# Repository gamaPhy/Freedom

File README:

## 3D Printing 
| Material      | Nozzle (C) | Bed (C) | Speed (mm/s) | First Layer speed | 
| ----------- | ----------- | -- | --| --|
| PLA+     | 220       | 50 | 60 | 40
| PETG   | 240        | 77 | 50 | 15

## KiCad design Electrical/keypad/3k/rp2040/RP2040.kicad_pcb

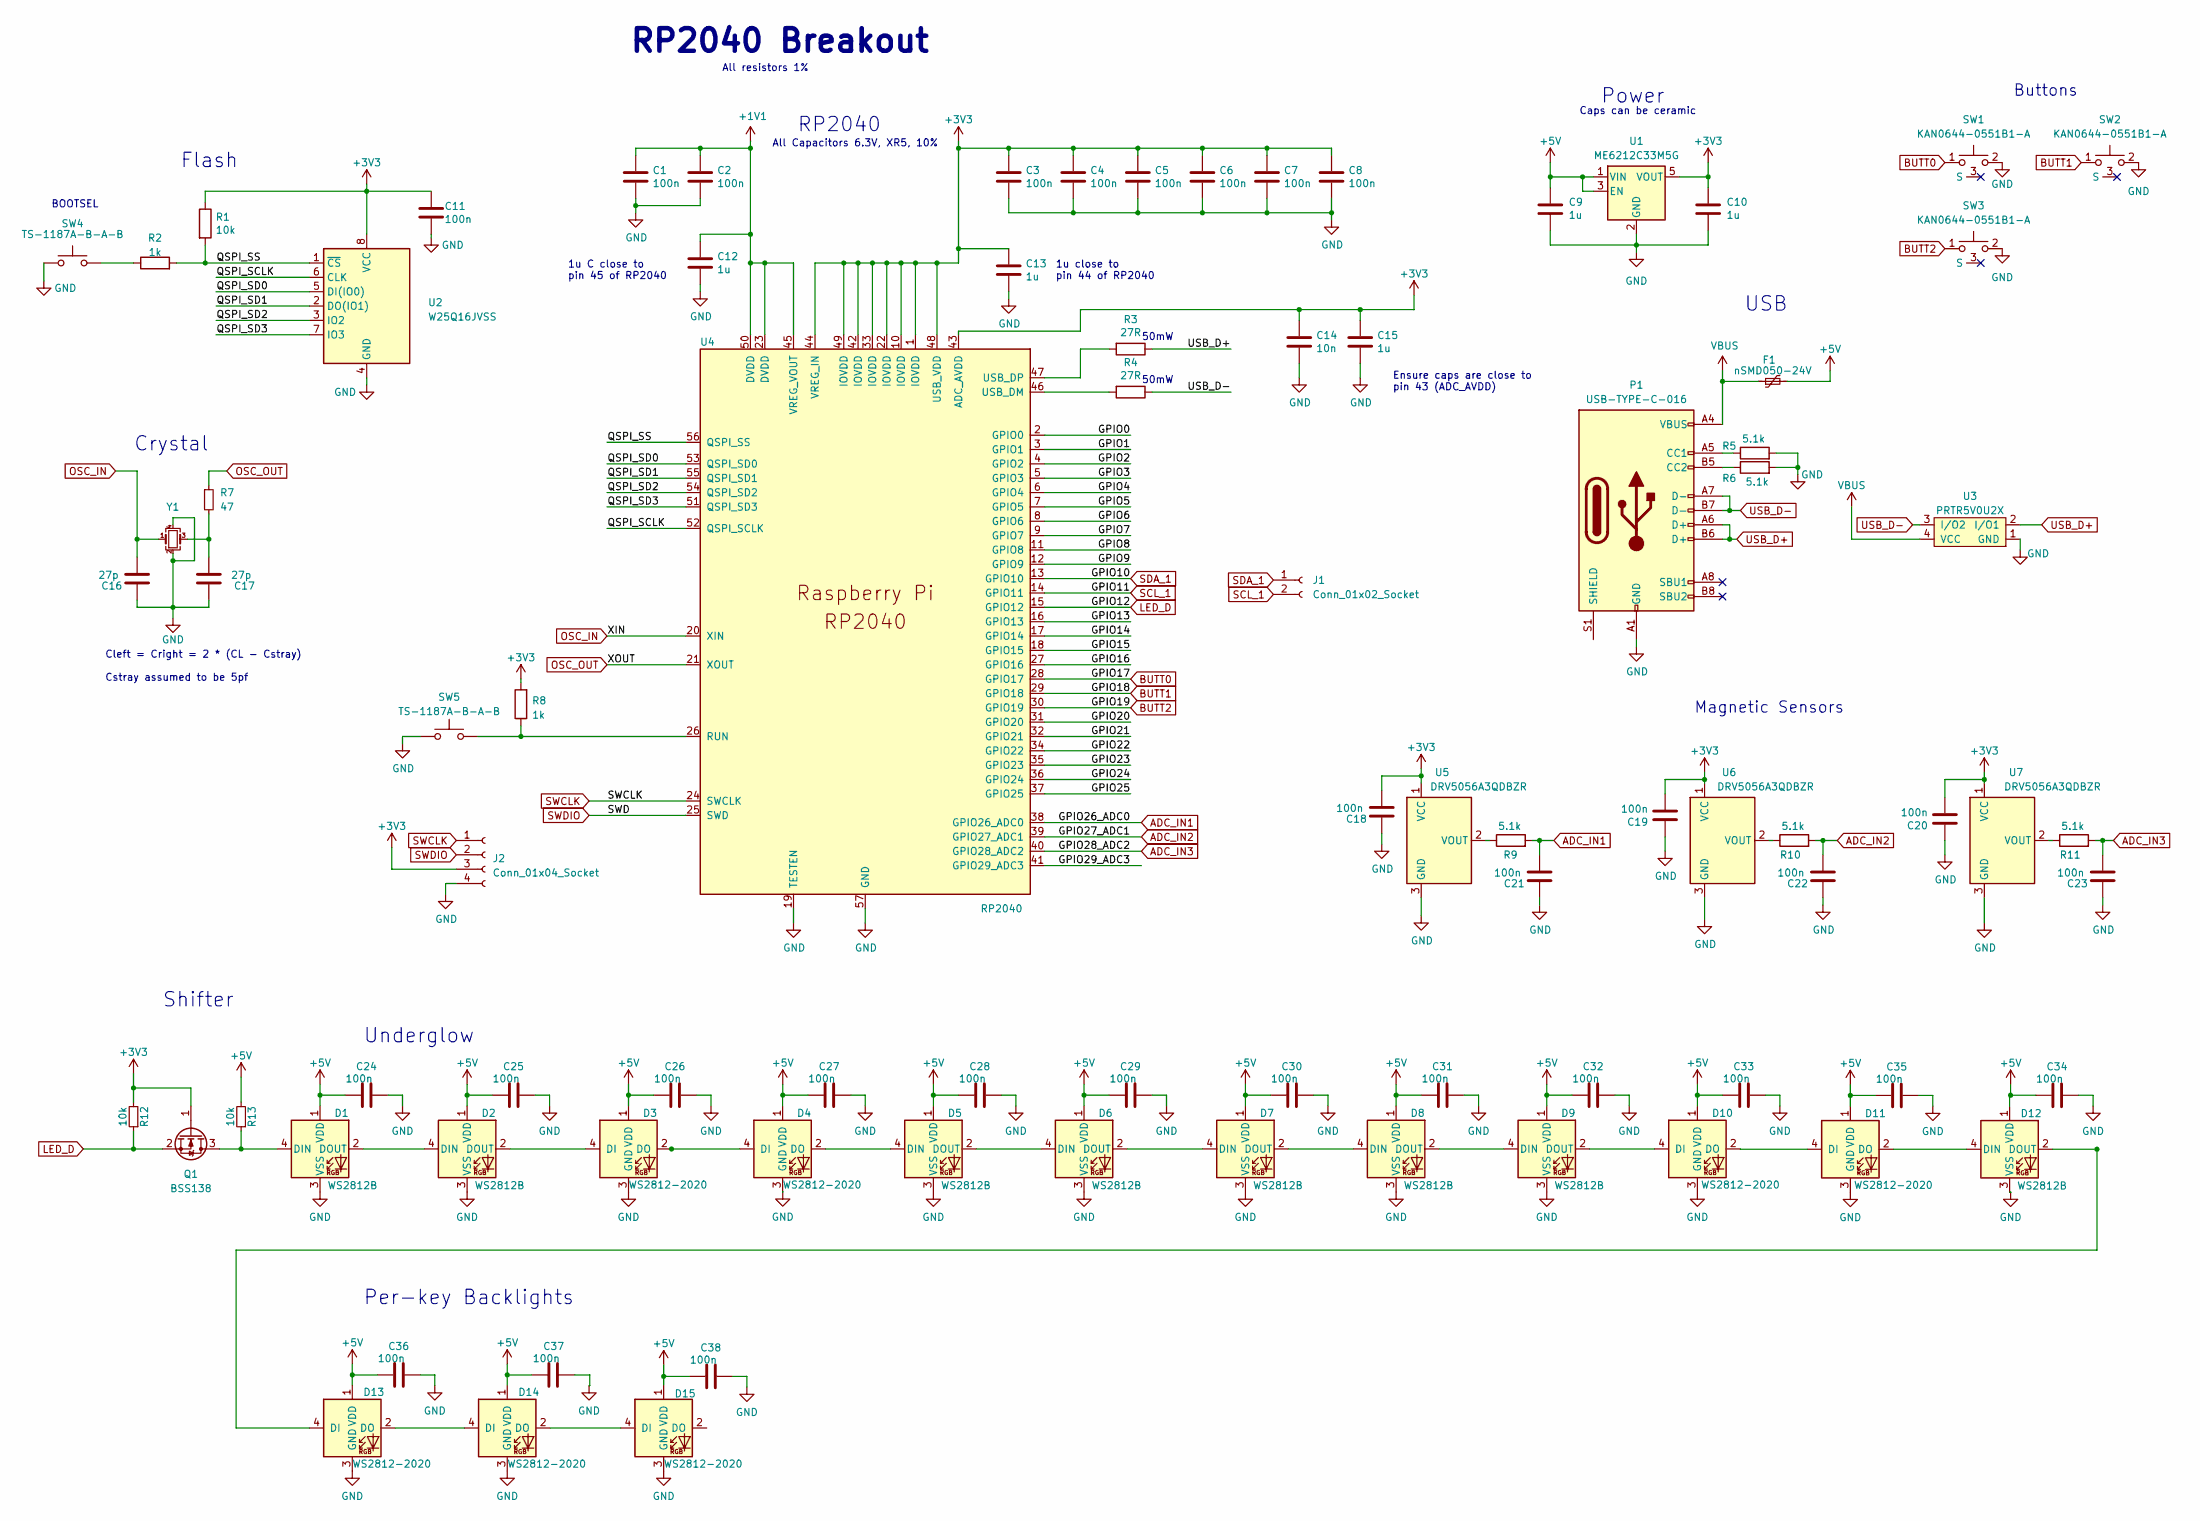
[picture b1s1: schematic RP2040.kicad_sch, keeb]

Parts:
C1, C2, C3, C4, C5, C6, C7, C8, C11, C18, C19, C20, C21, C22, C23, C24, C25, C26, C27, C28, C29, C30, C31, C32, C33, C34, C35, C36, C37, C38: 100n; C_0402_1005Metric
C9, C10: 1u; C_1206_3216Metric
C12, C13, C15: 1u; C_0402_1005Metric
C14: 10n; C_0402_1005Metric
C16, C17: 27p; C_0402_1005Metric
D1, D2, D5, D6, D7, D8, D9, D12: WS2812B; LED_WS2812B_PLCC4_5.0x5.0mm_P3.2mm
D3, D4, D10, D11, D13, D14, D15: WS2812-2020; LED_WS2812-2020; PARTREV V1.3
F1: nSMD050-24V; Fuse_1206_3216Metric
J1: Conn_01x02_Socket; PinSocket_1x02_P2.54mm_Vertical
J2: Conn_01x04_Socket; PinSocket_1x04_P2.54mm_Vertical
P1: USB-TYPE-C-016; USB-TYPE-C-016_Receptacle_DEALON_16P_MidMnt
Q1: BSS138; SOT-23
R1: 10k; R_0402_1005Metric
R2, R8: 1k; C_0402_1005Metric
R3, R4: 27R; C_0402_1005Metric
R5, R6, R9, R10, R11: 5.1k; C_0402_1005Metric
R7: 47; R_0402_1005Metric; LCSC Part # C25118
R12, R13: 10k; R_0402_1005Metric; LCSC Part # C25744
SW1, SW2, SW3: KAN0644-0551B1-A; KAN0644
SW4, SW5: TS-1187A-B-A-B; TS-1187A
U1: ME6212C33M5G; SOT-23-5
U2: W25Q16JVSS; SOIC-8_5.23x5.23mm_P1.27mm
U3: PRTR5V0U2X; SOT-143B
U4: RP2040; RP2040-QFN-56
U5, U6, U7: DRV5056A3QDBZR; SOT-23
Y1: 12MHz; Crystal_SMD_3225-4Pin_3.2x2.5mm; LCSC Part # C9002

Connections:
+1V1: C1.1, C2.1, C12.1, U4.23 (DVDD), U4.45 (VREG_VOUT), U4.50 (DVDD)
+3V3: C3.1, C4.1, C5.1, C6.1, C7.1, C8.1, C10.1, C11.1, C13.1, C14.1, C15.1, C18.2, C19.2, C20.2, J2.3, Q1.1 (G), R1.1, R8.2, R12.2, U1.5 (VOUT), U2.8 (VCC), U4.1 (IOVDD), U4.10 (IOVDD), U4.22 (IOVDD), U4.33 (IOVDD), U4.42 (IOVDD), U4.43 (ADC_AVDD), U4.44 (VREG_IN), U4.48 (USB_VDD), U4.49 (IOVDD), U5.1 (VCC), U6.1 (VCC), U7.1 (VCC)
+5V: C9.1, C24.1, C25.1, C26.1, C27.1, C28.1, C29.1, C30.1, C31.1, C32.1, C33.1, C34.1, C35.1, C36.1, C37.1, C38.1, D1.1 (VDD), D2.1 (VDD), D3.1 (VDD), D4.1 (VDD), D5.1 (VDD), D6.1 (VDD), D7.1 (VDD), D8.1 (VDD), D9.1 (VDD), D10.1 (VDD), D11.1 (VDD), D12.1 (VDD), D13.1 (VDD), D14.1 (VDD), D15.1 (VDD), F1.2, R13.2, U1.1 (VIN), U1.3 (EN)
/GPIO0: U4.2 (GPIO0)
/GPIO1: U4.3 (GPIO1)
/GPIO2: U4.4 (GPIO2)
/GPIO3: U4.5 (GPIO3)
/GPIO4: U4.6 (GPIO4)
/GPIO5: U4.7 (GPIO5)
/GPIO6: U4.8 (GPIO6)
/GPIO7: U4.9 (GPIO7)
/GPIO8: U4.11 (GPIO8)
/GPIO9: U4.12 (GPIO9)
/GPIO13: U4.16 (GPIO13)
/GPIO14: U4.17 (GPIO14)
/GPIO15: U4.18 (GPIO15)
/GPIO16: U4.27 (GPIO16)
/GPIO20: U4.31 (GPIO20)
/GPIO21: U4.32 (GPIO21)
/GPIO22: U4.34 (GPIO22)
/GPIO23: U4.35 (GPIO23)
/GPIO24: U4.36 (GPIO24)
/GPIO25: U4.37 (GPIO25)
/GPIO29_ADC3: U4.41 (GPIO29_ADC3)
/QSPI_SCLK: U2.6 (CLK), U4.52 (QSPI_SCLK)
/QSPI_SD0: U2.5 (DI(IO0)), U4.53 (QSPI_SD0)
/QSPI_SD1: U2.2 (DO(IO1)), U4.55 (QSPI_SD1)
/QSPI_SD2: U2.3 (IO2), U4.54 (QSPI_SD2)
/QSPI_SD3: U2.7 (IO3), U4.51 (QSPI_SD3)
/QSPI_SS: R1.2, R2.2, U2.1 (~CS), U4.56 (QSPI_SS)
ADC_IN1: C21.2, R9.2, U4.38 (GPIO26_ADC0)
ADC_IN2: C22.2, R10.2, U4.39 (GPIO27_ADC1)
ADC_IN3: C23.2, R11.2, U4.40 (GPIO28_ADC2)
BUTT0: SW1.1, U4.28 (GPIO17)
BUTT1: SW2.1, U4.29 (GPIO18)
BUTT2: SW3.1, U4.30 (GPIO19)
GND: C1.2, C2.2, C3.2, C4.2, C5.2, C6.2, C7.2, C8.2, C9.2, C10.2, C11.2, C12.2, C13.2, C14.2, C15.2, C16.1, C17.1, C18.1, C19.1, C20.1, C21.1, C22.1, C23.1, C24.2, C25.2, C26.2, C27.2, C28.2, C29.2, C30.2, C31.2, C32.2, C33.2, C34.2, C35.2, C36.2, C37.2, C38.2, D1.3 (VSS), D2.3 (VSS), D3.3 (GND), D4.3 (GND), D5.3 (VSS), D6.3 (VSS), D7.3 (VSS), D8.3 (VSS), D9.3 (VSS), D10.3 (GND), D11.3 (GND), D12.3 (VSS), D13.3 (GND), D14.3 (GND), D15.3 (GND), J2.4, P1.A1 (GND), P1.A12 (GND), P1.B1 (GND), P1.B12 (GND), R5.2, R6.2, SW1.2, SW2.2, SW3.2, SW4.1, SW5.1, U1.2 (GND), U2.4 (GND), U3.1 (GND), U4.19 (TESTEN), U4.57 (GND), U5.3 (GND), U6.3 (GND), U7.3 (GND), Y1.2, Y1.4
LED_D: Q1.2 (S), R12.1, U4.15 (GPIO12)
unnamed: C17.2, R7.2, Y1.3
unnamed: D1.4 (DIN), Q1.3 (D), R13.1
unnamed: D1.2 (DOUT), D2.4 (DIN)
unnamed: D2.2 (DOUT), D3.4 (DI)
unnamed: D3.2 (DO), D4.4 (DI)
unnamed: D4.2 (DO), D5.4 (DIN)
unnamed: D5.2 (DOUT), D6.4 (DIN)
unnamed: D6.2 (DOUT), D7.4 (DIN)
unnamed: D7.2 (DOUT), D8.4 (DIN)
unnamed: D8.2 (DOUT), D9.4 (DIN)
unnamed: D9.2 (DOUT), D10.4 (DI)
unnamed: D10.2 (DO), D11.4 (DI)
unnamed: D11.2 (DO), D12.4 (DIN)
unnamed: D12.2 (DOUT), D13.4 (DI)
unnamed: D13.2 (DO), D14.4 (DI)
unnamed: D14.2 (DO), D15.4 (DI)
unnamed: P1.A5 (CC1), R5.1
unnamed: P1.B5 (CC2), R6.1
unnamed: R2.1, SW4.2
unnamed: R8.1, SW5.2, U4.26 (RUN)
unnamed: R4.2, U4.46 (USB_DM)
unnamed: R3.2, U4.47 (USB_DP)
unnamed: R9.1, U5.2 (VOUT)
unnamed: R10.1, U6.2 (VOUT)
unnamed: R11.1, U7.2 (VOUT)
OSC_IN: C16.2, U4.20 (XIN), Y1.1
OSC_OUT: R7.1, U4.21 (XOUT)
SCL_1: J1.2, U4.14 (GPIO11)
SDA_1: J1.1, U4.13 (GPIO10)
SWCLK: J2.1, U4.24 (SWCLK)
SWDIO: J2.2, U4.25 (SWD)
USB_D+: P1.A6 (D+), P1.B6 (D+), R3.1, U3.2 (I/O1)
USB_D-: P1.A7 (D-), P1.B7 (D-), R4.1, U3.3 (I/O2)
VBUS: F1.1, P1.A4 (VBUS), P1.A9 (VBUS), P1.B4 (VBUS), P1.B9 (VBUS), U3.4 (VCC)

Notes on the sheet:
50mW
RP2040 Breakout
Underglow
Crystal
Magnetic Sensors
Per-key Backlights
All Capacitors 6.3V, XR5, 10%
USB
Flash
Ensure caps are close to pin 43 (ADC_AVDD)
1u close to pin 44 of RP2040
1u C close to pin 45 of RP2040
Caps can be ceramic
All resistors 1%
Power
Buttons
Shifter
RP2040
Cleft = Cright = 2 * (CL - Cstray) Cstray assumed to be 5pf
BOOTSEL

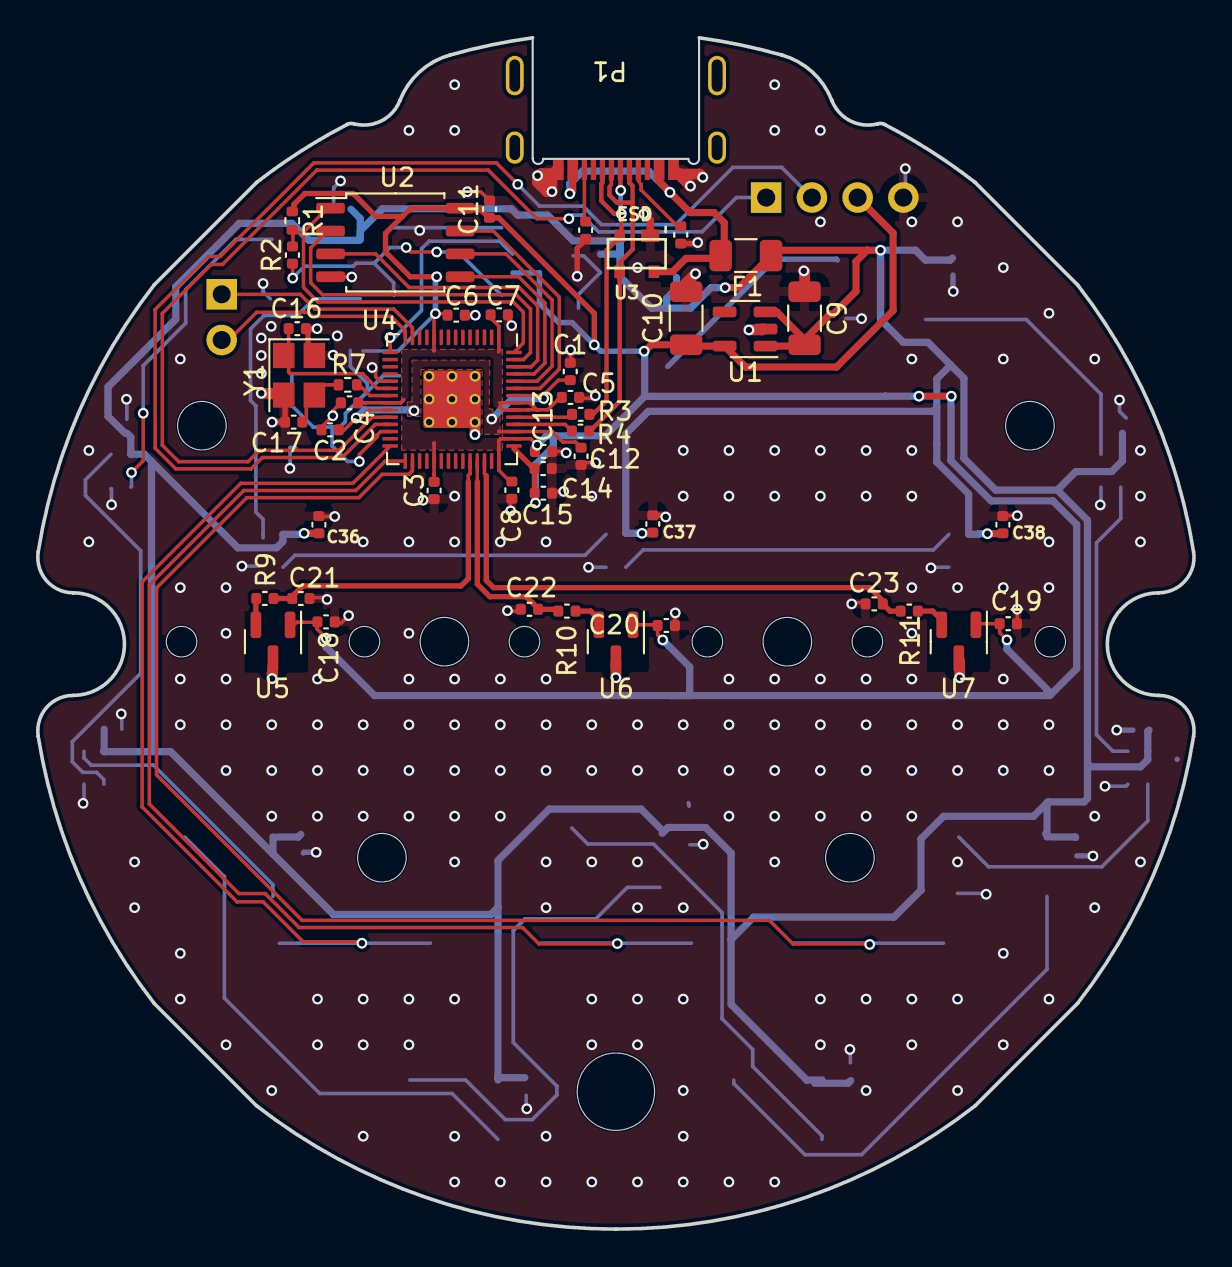
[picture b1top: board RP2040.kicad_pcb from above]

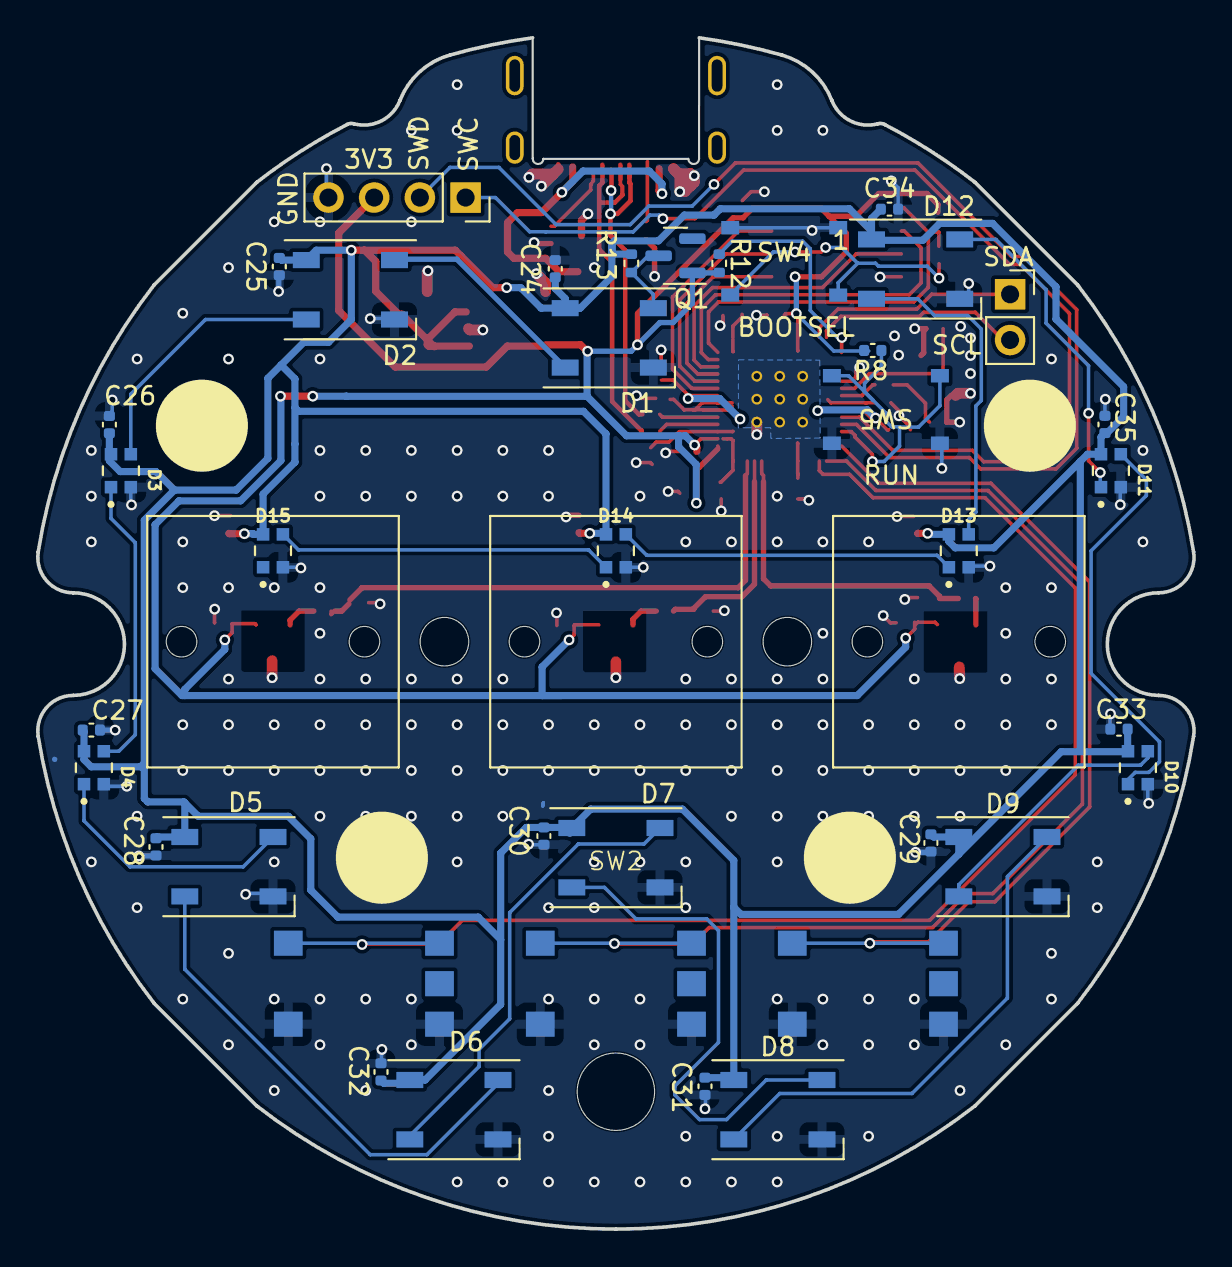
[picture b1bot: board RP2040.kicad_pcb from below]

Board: 4 copper layers, 64.2 x 66.2 mm, 84 parts (38 on the bottom side), 51 nets.

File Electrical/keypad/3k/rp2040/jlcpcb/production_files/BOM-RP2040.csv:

Comment,Designator,Footprint,LCSC
100n,"C1,C11,C18,C19,C2,C20,C21,C22,C23,C24,C25,C26,C27,C28,C29,C3,C30,C31,C32,C33,C34,C35,C36,C37,C38,C4,C5,C6,C7,C8",C_0402_1005Metric,C1525
47,R7,R_0402_1005Metric,C25118
10k,"R1,R12,R13",R_0402_1005Metric,C25744
1u,C12,C_0402_1005Metric,C52923
12MHz,Y1,Crystal_SMD_3225-4Pin_3.2x2.5mm,C9002
ME6212C33M5G,U1,SOT-23-5,
1u,C10,C_1206_3216Metric,
5.1k,R5,C_0402_1005Metric,
DRV5056A3QDBZR,U5,SOT-23,
BSS138,Q1,SOT-23,
PRTR5V0U2X,U3,SOT-143B,
1k,R2,C_0402_1005Metric,
1u,C9,C_1206_3216Metric,
1u,C13,C_0402_1005Metric,
27R,R3,C_0402_1005Metric,
USB-TYPE-C-016,P1,USB-TYPE-C-016_Receptacle_DEALON_16P_MidMnt,
nSMD050-24V,F1,Fuse_1206_3216Metric,
WS2812B,D2,LED_WS2812B_PLCC4_5.0x5.0mm_P3.2mm,
WS2812B,D5,LED_WS2812B_PLCC4_5.0x5.0mm_P3.2mm,
WS2812B,D7,LED_WS2812B_PLCC4_5.0x5.0mm_P3.2mm,
WS2812-2020,D3,LED_WS2812-2020,
WS2812B,D9,LED_WS2812B_PLCC4_5.0x5.0mm_P3.2mm,
KAN0644-0551B1-A,SW3,KAN0644,
WS2812B,D1,LED_WS2812B_PLCC4_5.0x5.0mm_P3.2mm,
WS2812B,D6,LED_WS2812B_PLCC4_5.0x5.0mm_P3.2mm,
WS2812B,D8,LED_WS2812B_PLCC4_5.0x5.0mm_P3.2mm,
WS2812-2020,D4,LED_WS2812-2020,
DRV5056A3QDBZR,U7,SOT-23,
TS-1187A-B-A-B,SW5,TS-1187A,
27R,R4,C_0402_1005Metric,
5.1k,R6,C_0402_1005Metric,
DRV5056A3QDBZR,U6,SOT-23,
TS-1187A-B-A-B,SW4,TS-1187A,
WS2812-2020,D10,LED_WS2812-2020,
KAN0644-0551B1-A,SW1,KAN0644,
1k,R8,C_0402_1005Metric,
KAN0644-0551B1-A,SW2,KAN0644,
5.1k,R9,C_0402_1005Metric,
5.1k,R10,C_0402_1005Metric,
WS2812-2020,D11,LED_WS2812-2020,
1u,C15,C_0402_1005Metric,
27p,C17,C_0402_1005Metric,
10n,C14,C_0402_1005Metric,
5.1k,R11,C_0402_1005Metric,
W25Q16JVSS,U2,SOIC-8_5.23x5.23mm_P1.27mm,
27p,C16,C_0402_1005Metric,
RP2040,U4,RP2040-QFN-56,
WS2812B,D12,LED_WS2812B_PLCC4_5.0x5.0mm_P3.2mm,
WS2812-2020,D14,LED_WS2812-2020,
WS2812-2020,D13,LED_WS2812-2020,
WS2812-2020,D15,LED_WS2812-2020,

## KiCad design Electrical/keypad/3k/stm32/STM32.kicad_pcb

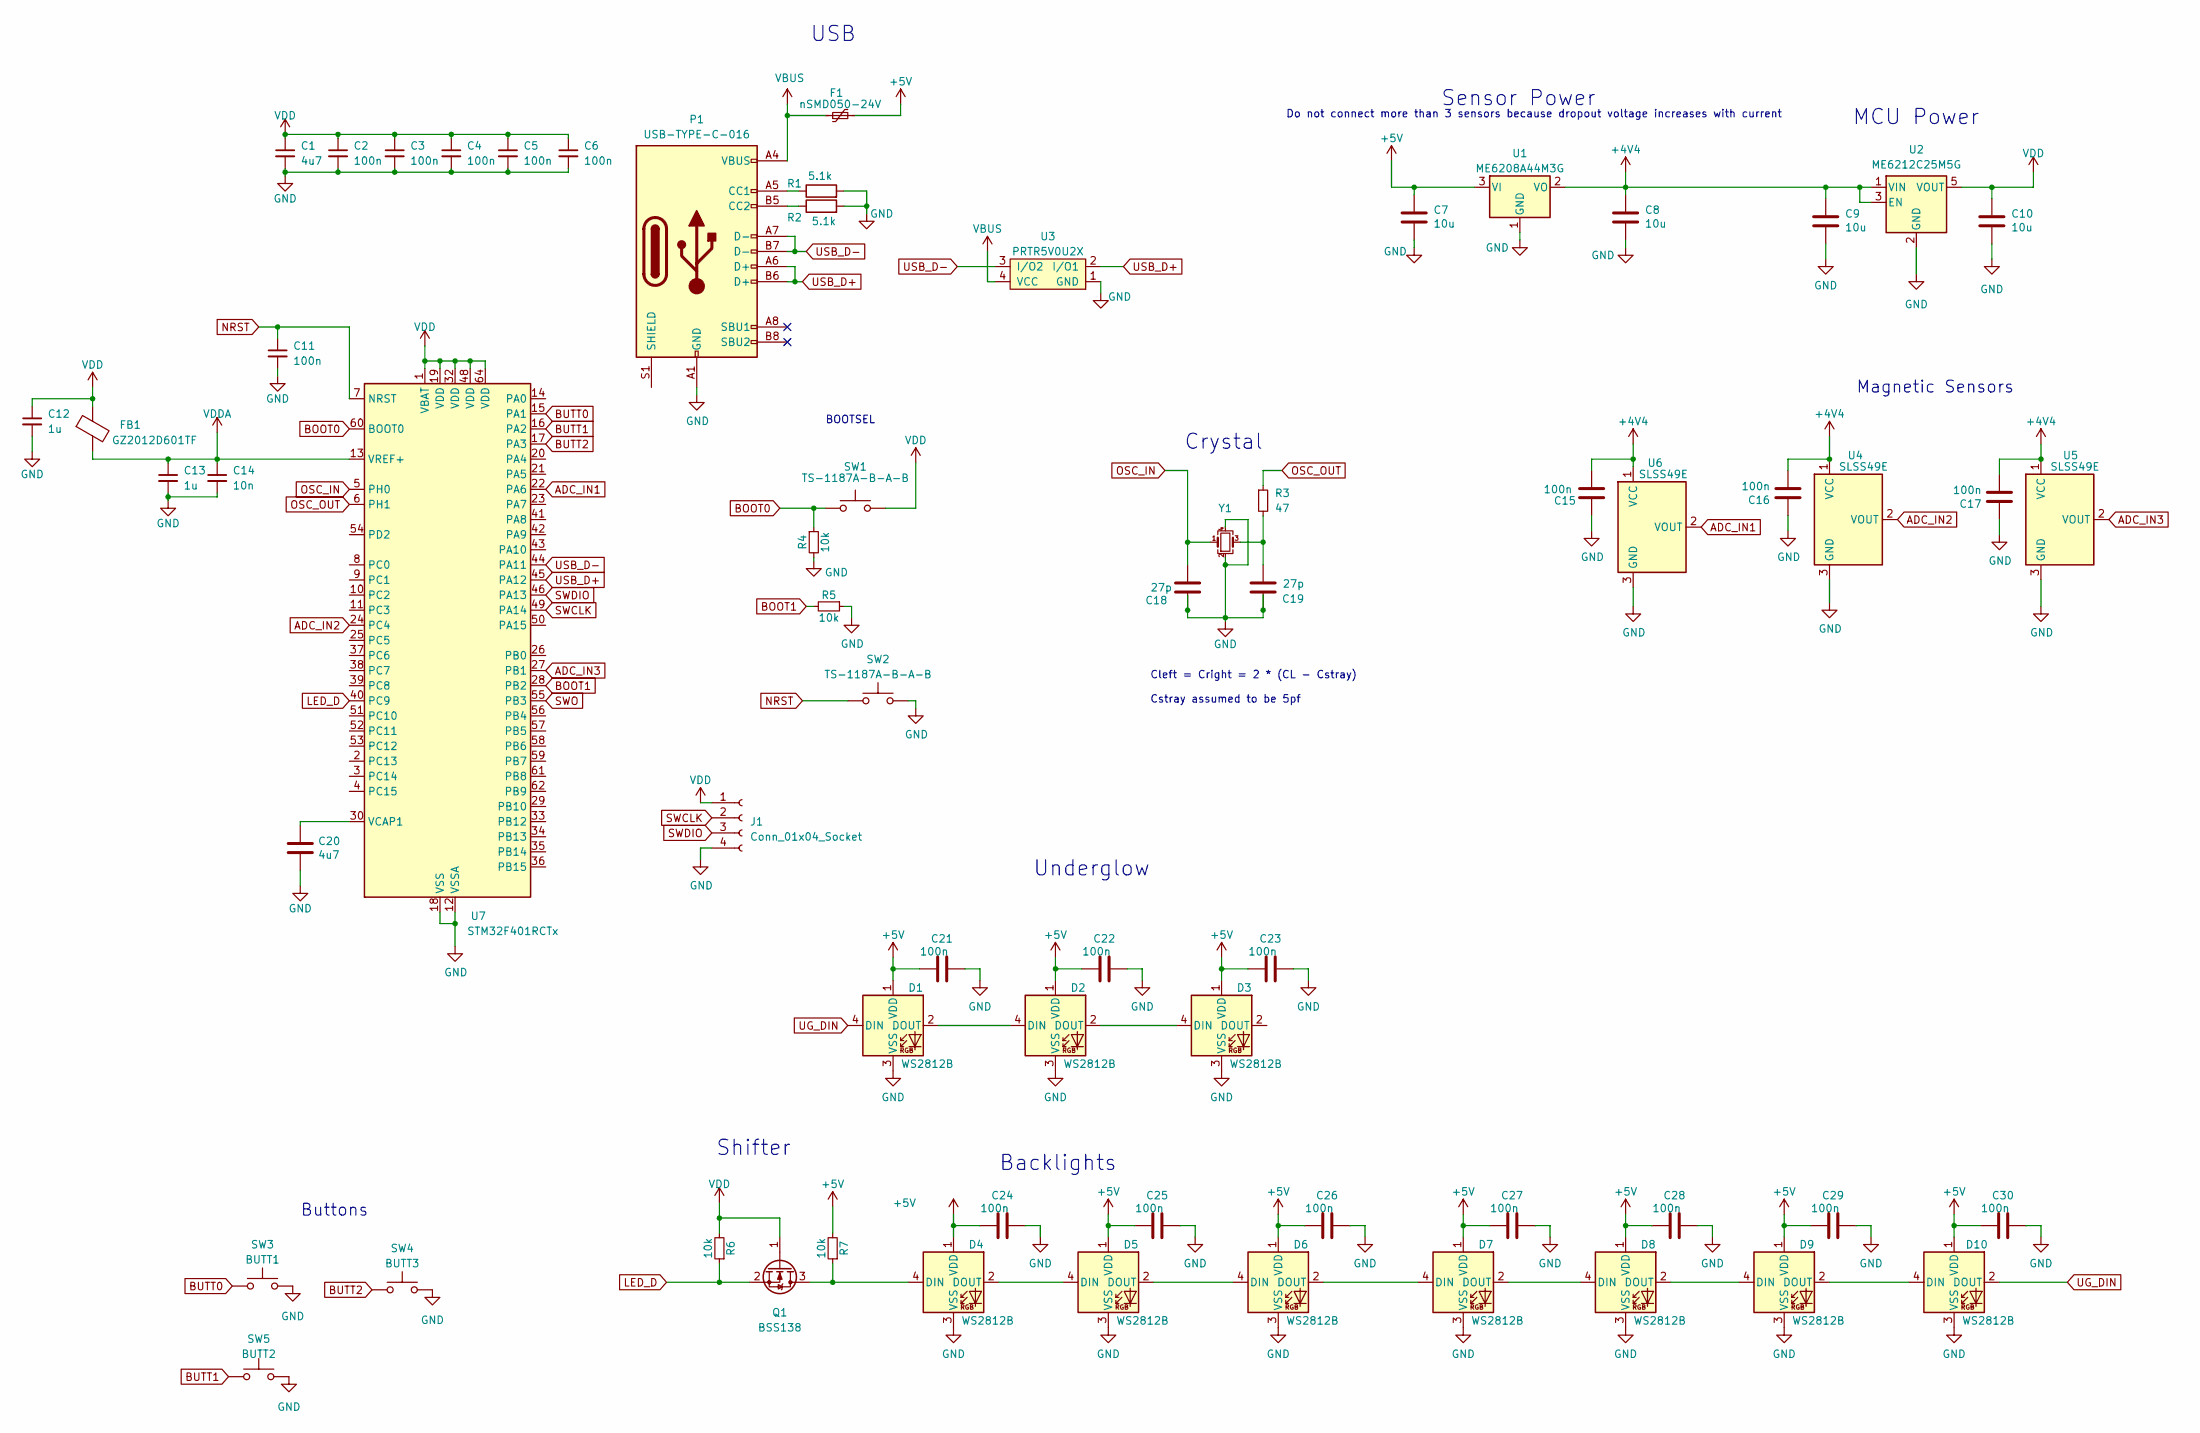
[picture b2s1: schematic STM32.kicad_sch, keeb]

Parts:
C1: 4u7; C_0603_1608Metric; LCSC Part # C19666
C2, C3, C4, C5, C6, C11: 100n; C_0402_1005Metric; LCSC Part # C1525
C7, C8, C9, C10: 10u; C_1206_3216Metric
C12, C13: 1u; C_0402_1005Metric; LCSC Part # C52923
C14: 10n; C_0402_1005Metric; LCSC Part # C15195
C15, C16, C17, C21, C22, C23, C24, C25, C26, C27, C28, C29, C30: 100n; C_0402_1005Metric
C18, C19: 27p; C_0402_1005Metric
C20: 4u7; C_0805_2012Metric
D1, D2, D3, D4, D5, D6, D7, D8, D9, D10: WS2812B; LED_WS2812B_PLCC4_5.0x5.0mm_P3.2mm
F1: nSMD050-24V; Fuse_1206_3216Metric
FB1: GZ2012D601TF; C_0805_2012Metric
J1: Conn_01x04_Socket; PinSocket_1x04_P2.54mm_Vertical
P1: USB-TYPE-C-016; USB-TYPE-C-016_Receptacle_DEALON_16P_MidMnt
Q1: BSS138; SOT-23
R1, R2: 5.1k; C_0402_1005Metric
R3: 47; R_0402_1005Metric; LCSC Part # C25118
R4, R5, R6, R7: 10k; R_0402_1005Metric; LCSC Part # C25744
SW1, SW2: TS-1187A-B-A-B; TS-1187A
SW3: BUTT1; SW_Push_1P1T_NO_6x6mm_H9.5mm
SW4: BUTT3; SW_Push_1P1T_NO_6x6mm_H9.5mm
SW5: BUTT2; SW_Push_1P1T_NO_6x6mm_H9.5mm
U1: ME6208A44M3G; SOT-23-3
U2: ME6212C25M5G; SOT-23-5
U3: PRTR5V0U2X; SOT-143B
U4, U5, U6: SLSS49E; SOT-23
U7: STM32F401RCTx; LQFP-64_10x10mm_P0.5mm
Y1: 12MHz; Crystal_SMD_3225-4Pin_3.2x2.5mm; LCSC Part # C9002

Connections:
+4V4: C8.1, C9.1, C15.2, C16.2, C17.2, U1.2 (VO), U2.1 (VIN), U2.3 (EN), U4.1 (VCC), U5.1 (VCC), U6.1 (VCC)
+5V: C7.1, C21.1, C22.1, C23.1, C24.1, C25.1, C26.1, C27.1, C28.1, C29.1, C30.1, D1.1 (VDD), D2.1 (VDD), D3.1 (VDD), D4.1 (VDD), D5.1 (VDD), D6.1 (VDD), D7.1 (VDD), D8.1 (VDD), D9.1 (VDD), D10.1 (VDD), F1.2, R7.2, U1.3 (VI)
ADC_IN1: U6.2 (VOUT), U7.22 (PA6)
ADC_IN2: U4.2 (VOUT), U7.24 (PC4)
ADC_IN3: U5.2 (VOUT), U7.27 (PB1)
BOOT0: R4.1, SW1.1, U7.60 (BOOT0)
BOOT1: R5.2, U7.28 (PB2)
BUTT0: SW3.1, U7.15 (PA1)
BUTT1: SW5.1, U7.16 (PA2)
BUTT2: SW4.1, U7.17 (PA3)
GND: C1.2, C2.2, C3.2, C4.2, C5.2, C6.2, C7.2, C8.2, C9.2, C10.2, C11.2, C12.2, C13.2, C14.2, C15.1, C16.1, C17.1, C18.1, C19.1, C20.2, C21.2, C22.2, C23.2, C24.2, C25.2, C26.2, C27.2, C28.2, C29.2, C30.2, D1.3 (VSS), D2.3 (VSS), D3.3 (VSS), D4.3 (VSS), D5.3 (VSS), D6.3 (VSS), D7.3 (VSS), D8.3 (VSS), D9.3 (VSS), D10.3 (VSS), J1.4, P1.A1 (GND), P1.A12 (GND), P1.B1 (GND), P1.B12 (GND), R1.2, R2.2, R4.2, R5.1, SW2.2, SW3.2, SW4.2, SW5.2, U1.1 (GND), U2.2 (GND), U3.1 (GND), U4.3 (GND), U5.3 (GND), U6.3 (GND), U7.12 (VSSA), U7.18 (VSS), U7.31 (VSS), U7.47 (VSS), U7.63 (VSS), Y1.2, Y1.4
LED_D: Q1.2 (S), R6.1, U7.40 (PC9)
NRST: C11.1, SW2.1, U7.7 (NRST)
unnamed: C19.2, R3.2, Y1.3
unnamed: D1.2 (DOUT), D2.4 (DIN)
unnamed: D2.2 (DOUT), D3.4 (DIN)
unnamed: D4.4 (DIN), Q1.3 (D), R7.1
unnamed: D4.2 (DOUT), D5.4 (DIN)
unnamed: D5.2 (DOUT), D6.4 (DIN)
unnamed: D6.2 (DOUT), D7.4 (DIN)
unnamed: D7.2 (DOUT), D8.4 (DIN)
unnamed: D8.2 (DOUT), D9.4 (DIN)
unnamed: D9.2 (DOUT), D10.4 (DIN)
unnamed: P1.A5 (CC1), R1.1
unnamed: P1.B5 (CC2), R2.1
unnamed: C20.1, U7.30 (VCAP1)
OSC_IN: C18.2, U7.5 (PH0), Y1.1
OSC_OUT: R3.1, U7.6 (PH1)
SWCLK: J1.2, U7.49 (PA14)
SWDIO: J1.3, U7.46 (PA13)
SWO: U7.55 (PB3)
UG_DIN: D1.4 (DIN), D10.2 (DOUT)
USB_D+: P1.A6 (D+), P1.B6 (D+), U3.2 (I/O1), U7.45 (PA12)
USB_D-: P1.A7 (D-), P1.B7 (D-), U3.3 (I/O2), U7.44 (PA11)
VBUS: F1.1, P1.A4 (VBUS), P1.A9 (VBUS), P1.B4 (VBUS), P1.B9 (VBUS), U3.4 (VCC)
VDD: C1.1, C2.1, C3.1, C4.1, C5.1, C6.1, C10.1, C12.1, FB1.1, J1.1, Q1.1 (G), R6.2, SW1.2, U2.5 (VOUT), U7.1 (VBAT), U7.19 (VDD), U7.32 (VDD), U7.48 (VDD), U7.64 (VDD)
VDDA: C13.1, C14.1, FB1.2, U7.13 (VREF+)

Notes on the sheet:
Sensor Power
Do not connect more than 3 sensors because dropout voltage increases with current
BOOTSEL
Backlights
Crystal
MCU Power
Magnetic Sensors
Underglow
USB
Buttons
Shifter
Cleft = Cright = 2 * (CL - Cstray) Cstray assumed to be 5pf

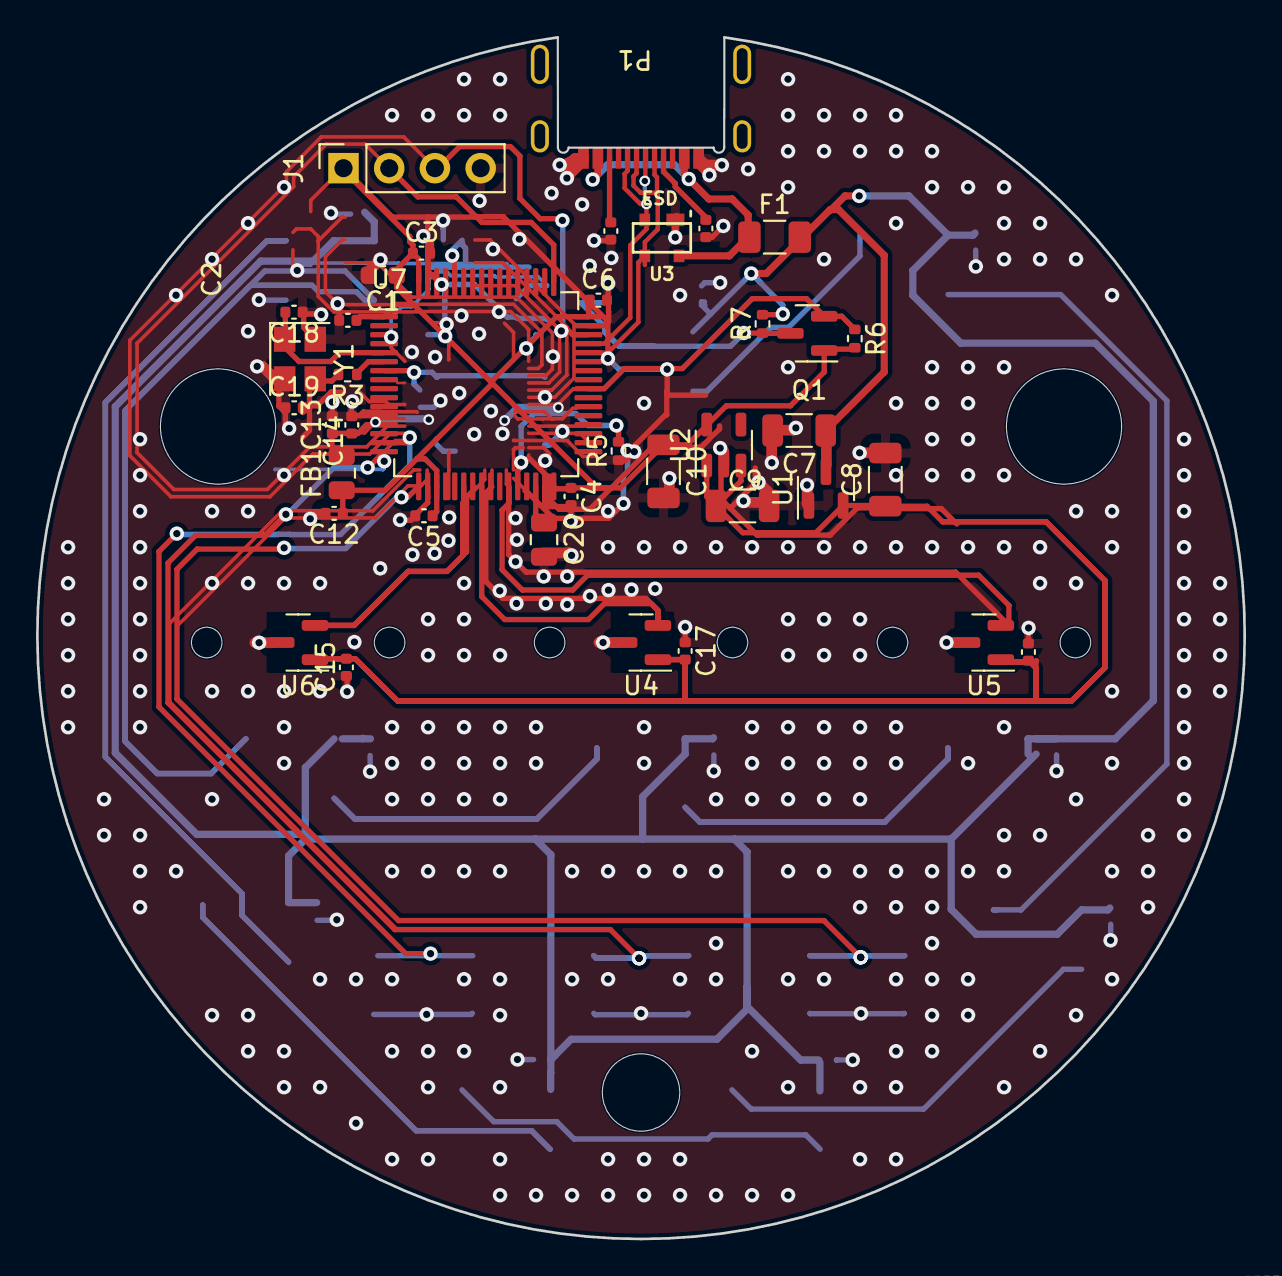
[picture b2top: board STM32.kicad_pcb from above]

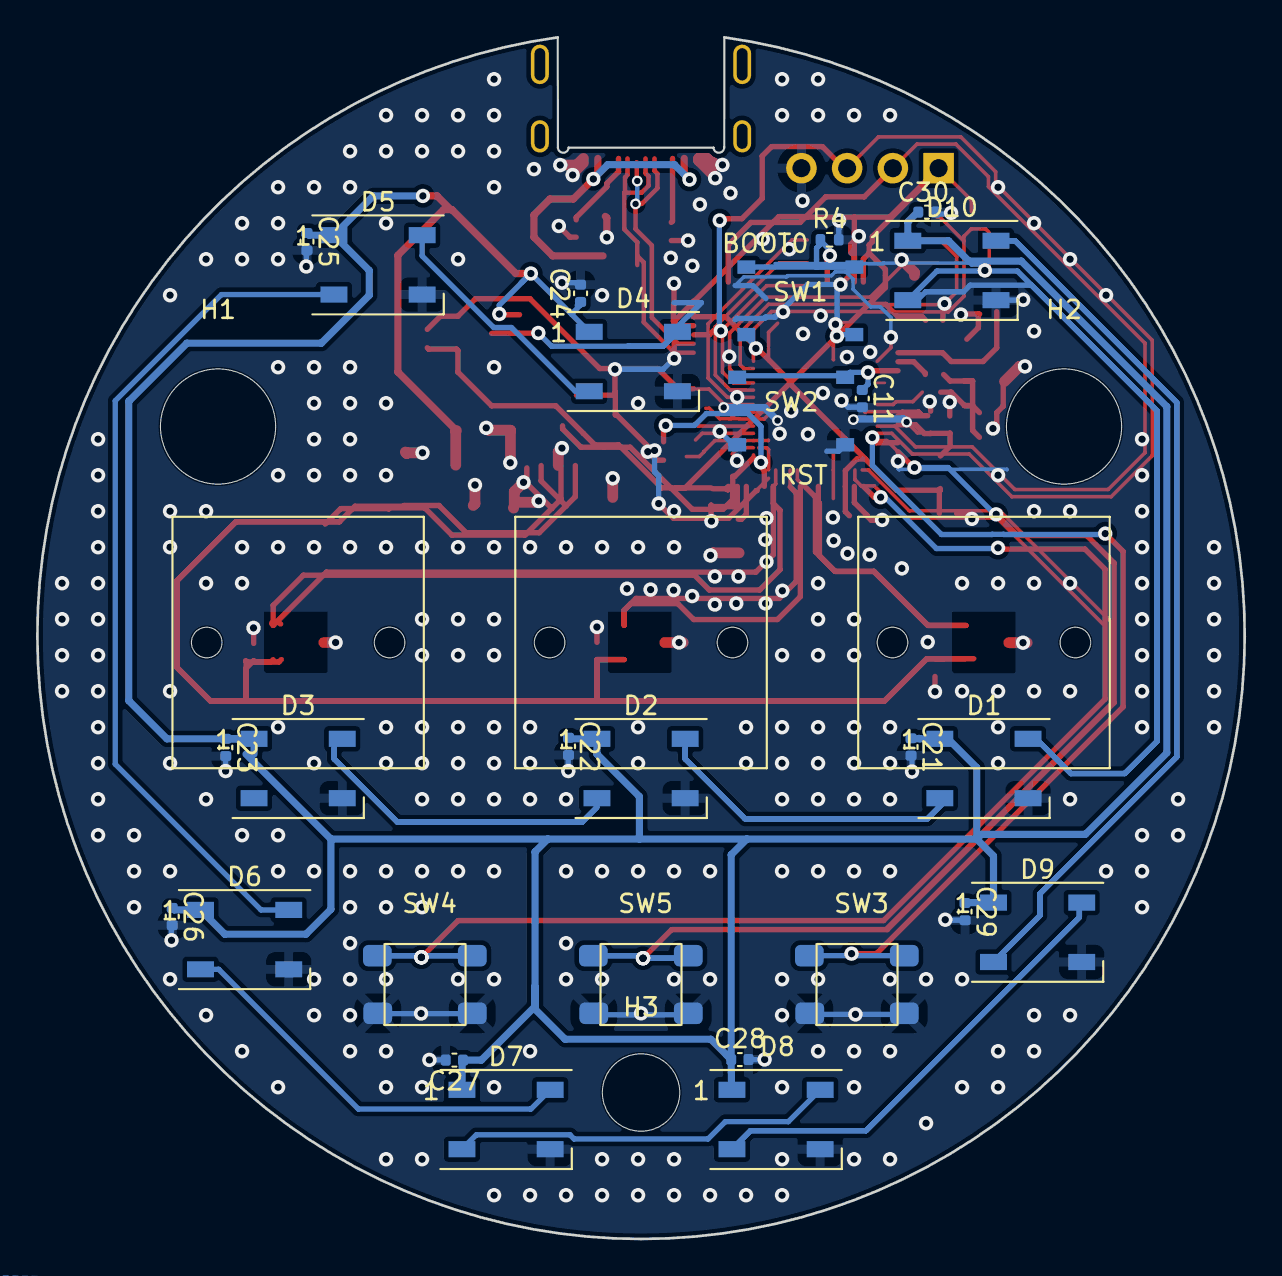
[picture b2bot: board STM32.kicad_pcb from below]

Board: 4 copper layers, 67.1 x 66.8 mm, 68 parts (30 on the bottom side), 36 nets.

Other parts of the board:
H1, H2: MountingHole_6.4mm_M6_DIN965
H3: MountingHole_4.3mm_M4_DIN965

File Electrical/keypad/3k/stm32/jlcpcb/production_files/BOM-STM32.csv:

Comment,Designator,Footprint,LCSC
10n,C14,C_0402_1005Metric,C15195
100n,"C11,C2,C3,C4,C5,C6",C_0402_1005Metric,C1525
4u7,C1,C_0603_1608Metric,C19666
47,R3,R_0402_1005Metric,C25118
10k,"R4,R5,R6,R7",R_0402_1005Metric,C25744
1u,"C12,C13",C_0402_1005Metric,C52923
12MHz,Y1,Crystal_SMD_3225-4Pin_3.2x2.5mm,C9002
10u,C8,C_1206_3216Metric,
ME6208A44M3G,U1,SOT-23,
100n,C17,C_0402_1005Metric,
10u,C7,C_1206_3216Metric,
10u,C10,C_1206_3216Metric,
SLSS49E,U5,SOT-23,
100n,C16,C_0402_1005Metric,
100n,C15,C_0402_1005Metric,
BSS138,Q1,SOT-23,
5.1k,R1,C_0402_1005Metric,
PRTR5V0U2X,U3,SOT-143B,
ME6212C25M5G,U2,SOT-23-5,
5.1k,R2,C_0402_1005Metric,
27p,C18,C_0402_1005Metric,
10u,C9,C_1206_3216Metric,
4u7,C20,C_0805_2012Metric,
27p,C19,C_0402_1005Metric,
USB-TYPE-C-016,P1,USB-TYPE-C-016_Receptacle_DEALON_16P_MidMnt,
nSMD050-24V,F1,Fuse_1206_3216Metric,
100n,C26,C_0402_1005Metric,
100n,C29,C_0402_1005Metric,
100n,C25,C_0402_1005Metric,
100n,C27,C_0402_1005Metric,
WS2812B,D2,LED_WS2812B_PLCC4_5.0x5.0mm_P3.2mm,
100n,C21,C_0402_1005Metric,
100n,C22,C_0402_1005Metric,
WS2812B,D5,LED_WS2812B_PLCC4_5.0x5.0mm_P3.2mm,
100n,C23,C_0402_1005Metric,
WS2812B,D7,LED_WS2812B_PLCC4_5.0x5.0mm_P3.2mm,
WS2812B,D3,LED_WS2812B_PLCC4_5.0x5.0mm_P3.2mm,
WS2812B,D9,LED_WS2812B_PLCC4_5.0x5.0mm_P3.2mm,
BUTT1,SW3,PTS647_4.5x4.5mm,
WS2812B,D1,LED_WS2812B_PLCC4_5.0x5.0mm_P3.2mm,
WS2812B,D6,LED_WS2812B_PLCC4_5.0x5.0mm_P3.2mm,
WS2812B,D8,LED_WS2812B_PLCC4_5.0x5.0mm_P3.2mm,
100n,C28,C_0402_1005Metric,
WS2812B,D4,LED_WS2812B_PLCC4_5.0x5.0mm_P3.2mm,
100n,C24,C_0402_1005Metric,
GZ2012D601TF,FB1,C_0805_2012Metric,
STM32F401RCTx,U7,LQFP-64_10x10mm_P0.5mm,
Conn_01x04_Socket,J1,PinSocket_1x04_P2.54mm_Vertical,
BUTT2,SW5,PTS647_4.5x4.5mm,
SLSS49E,U4,SOT-23,
SLSS49E,U6,SOT-23,
BUTT3,SW4,PTS647_4.5x4.5mm,
WS2812B,D10,LED_WS2812B_PLCC4_5.0x5.0mm_P3.2mm,
100n,C30,C_0402_1005Metric,
TS-1187A-B-A-B,SW2,TS-1187A,
TS-1187A-B-A-B,SW1,TS-1187A,
